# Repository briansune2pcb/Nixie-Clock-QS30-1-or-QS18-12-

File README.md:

# Nixie-Clock-QS30-1-or-QS18-12-

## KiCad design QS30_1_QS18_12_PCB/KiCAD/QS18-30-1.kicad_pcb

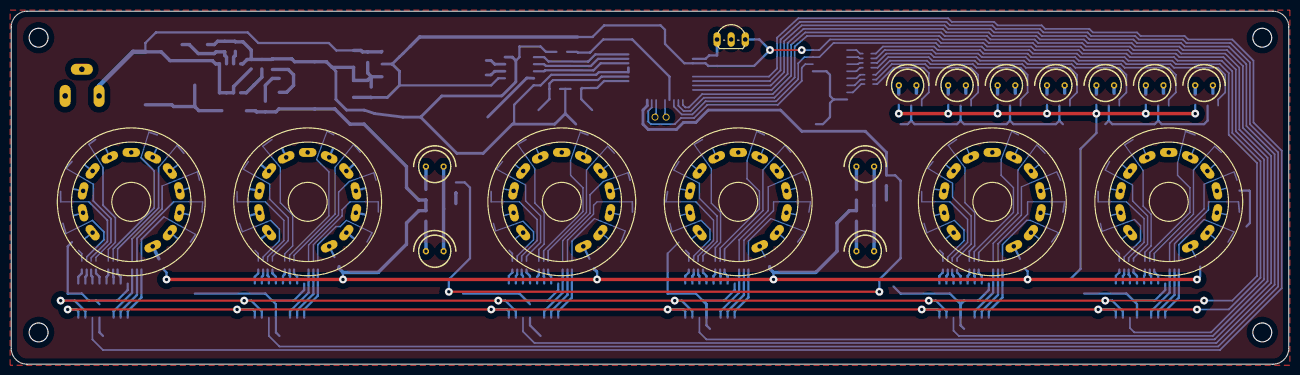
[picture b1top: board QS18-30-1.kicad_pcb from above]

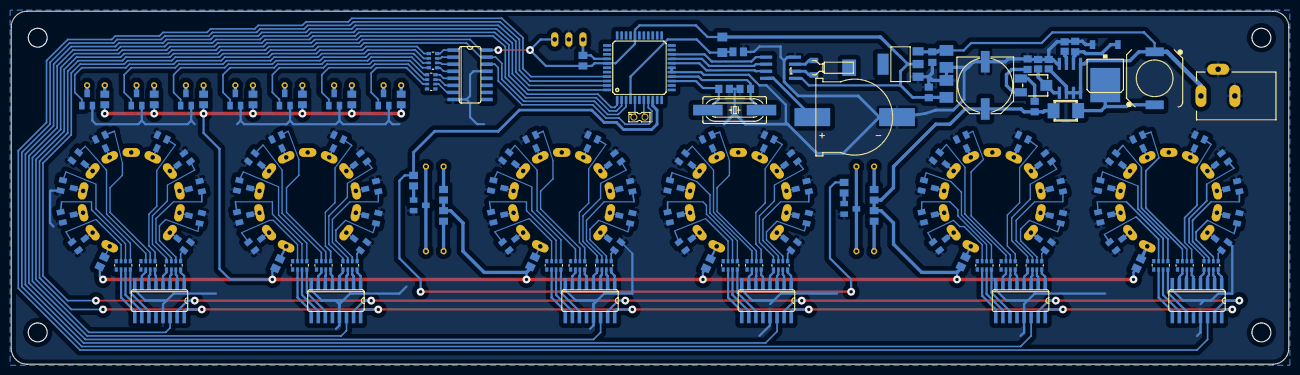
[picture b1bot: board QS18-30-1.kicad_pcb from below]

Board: 2 copper layers, 229.9 x 63.5 mm, 162 parts (144 on the bottom side), 253 nets.

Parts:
C1, C2, C3, C5, C6, C8, C10: C0805
C4: C1206
C7, C9: B_3528-21R
C11: PANASONIC_G
D1: SMB
IC1, IC2, IC3, IC4, IC5, IC6, IC9: 4017D; SO16
IC7: MC34063AD; SOIC8
J1: DCJ0303
L2: DR1033
MCU1: AT89S51-33P; TQFP44
N1, N2, N3, N4, N5, N6, N7, N8, N9, N10: IN-3
N11: Mon; IN-3
Q1: HC49UP
Q3: IRFR5305; D-PAK_TO252AA
R1, R2, R3, R4, R16, R17, R18, R19, R24, R25, R26, R27, R30, R31, R32, R33, R34, R35, R43, R44: EXB38V
R5, R6, R7, R8, R9, R10, R14, R15, R20, R21, R22, R28, R29, R36, R37, R38, R39, R40, R41, R42, R45: M0805
R11, R12, R13: R0805
R23: RTRIM3374
REG2: REG1117; SOT223
T1, T2, T3, T4, T5, T6, T7, T8, T9, T10, T11, T12, T13, T14, T15, T16, T17, T18, T19, T20, T21, T22, T23, T24, T25, T26, T27, T28, T29, T30, T31, T32, T33, T34, T35, T36, T37, T38, T39, T40, T41, T42, T43, T44, T45, T46, T47, T48, T49, T50, T51, T52, T53, T54, T55, T56, T57, T58, T59, T60, T61, T62, T63, T64, T65, T66, T67, T68, T69: SOT23-BEC
TUBE1, TUBE2, TUBE3, TUBE4, TUBE5, TUBE6: QS30-1R1; QS30-1_V3
U$1: DS1302SOP08; SOP08
U$2: 1220BATTERY_SF; 1220BATTERY
U$3: MS1V-T1K-6P; MS1V-T1K
U$4: HX1838; TO92-
X1: 332-02

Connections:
170V: C11.+, D1.1, R5.2, R6.2, R7.2, R8.2, R9.2, R10.2, R11.2, R14.2, R15.2, R28.2, R29.2, R36.2, R37.2, R38.2, R39.2, R40.2, R41.2, R42.2
+5V: C4.2, C9.+, C10.1, IC1.16, IC2.16, IC3.16, IC4.16, IC5.16, IC6.16, IC9.16, MCU1.29, MCU1.38, R45.2, REG2.2, U$1.1, U$4.1
+12V: C2.1, C7.+, C8.1, IC7.1, IC7.6, IC7.7, IC7.8, J1.1, L2.1, REG2.3
CLK_D0: IC9.14, MCU1.8
CLK_H0: IC1.14, MCU1.41
CLK_H1: IC2.14, MCU1.42
CLK_M0: IC3.14, MCU1.43
CLK_M1: IC4.14, MCU1.44
CLK_S0: IC5.14, MCU1.1
CLK_S1: IC6.14, MCU1.2
CS: MCU1.20, U$1.5
DAY0: R43.1, T63.B
DAY1: R43.2, T64.B
DAY2: R43.3, T65.B
DAY3: R43.4, T66.B
DAY4: R44.1, T67.B
DAY5: R44.2, T68.B
DAY6: R44.3, T69.B
DOT: MCU1.9, R20.2, R21.2
GND: C1.2, C2.2, C3.2, C5.2, C6.1, C7.-, C8.2, C9.-, C10.2, C11.-, IC1.8, IC1.13, IC2.8, IC2.13, IC3.8, IC3.13, IC4.8, IC4.13, IC5.8, IC5.13, IC6.8, IC6.13, IC7.4, IC9.8, IC9.13, J1.2, J1.3, MCU1.16, MCU1.17, Q3.3, R12.1, R13.1, R22.1, REG2.1, T1.E, T2.E, T3.E, T4.E, T5.E, T6.E, T7.E, T8.E, T9.E, T10.E, T11.E, T12.E, T13.E, T14.E, T15.E, T16.E, T17.E, T18.E, T19.E, T20.E, T21.E, T22.E, T23.E, T24.E, T25.E, T26.E, T27.E, T28.E, T29.E, T30.E, T31.E, T32.E, T33.E, T34.E, T35.E, T36.E, T37.E, T38.E, T39.E, T40.E, T41.E, T42.E, T43.E, T44.E, T45.E, T46.E, T47.E, T48.E, T49.E, T50.E, T51.E, T52.E, T53.E, T54.E, T55.E, T56.E, T57.E, T58.E, T59.E, T60.E, T61.E, T62.E, T63.E, T64.E, T65.E, T66.E, T67.E, T68.E, T69.E, U$1.4, U$2.-, U$4.2
unnamed: C5.1, MCU1.14, Q1.1
unnamed: C6.2, MCU1.15, Q1.2
unnamed: R1.1, T2.B
unnamed: R1.2, T3.B
unnamed: R1.3, T4.B
unnamed: R4.1, T12.B
unnamed: R1.4, T5.B
unnamed: R2.1, T6.B
unnamed: R2.2, T7.B
unnamed: R2.3, T8.B
unnamed: R3.1, T9.B
unnamed: R3.2, T10.B
unnamed: R3.3, T1.B
unnamed: R4.2, T13.B
unnamed: R4.3, T14.B
unnamed: R4.4, T15.B
unnamed: R16.1, T16.B
unnamed: R16.2, T17.B
unnamed: R16.3, T18.B
unnamed: R17.1, T19.B
unnamed: R17.2, T20.B
unnamed: R17.3, T11.B
unnamed: R14.1, TUBE3.A
unnamed: R15.1, TUBE4.A
unnamed: R5.1, TUBE1.A
unnamed: R18.1, T22.B
unnamed: R6.1, TUBE2.A
unnamed: R18.2, T23.B
unnamed: R18.3, T24.B
unnamed: R18.4, T25.B
unnamed: R19.1, T26.B
unnamed: R19.2, T27.B
unnamed: R19.3, T28.B
unnamed: R24.1, T29.B
unnamed: R24.2, T30.B
unnamed: R24.3, T21.B
unnamed: R25.1, T32.B
unnamed: R25.2, T33.B
unnamed: R25.3, T34.B
unnamed: R25.4, T35.B
unnamed: R26.1, T36.B
unnamed: R26.2, T37.B
unnamed: R26.3, T38.B
unnamed: R27.1, T39.B
unnamed: R27.2, T40.B
unnamed: R27.3, T31.B
unnamed: IC3.1, R18.8
unnamed: IC3.2, R18.7
unnamed: N3.A, R7.1
unnamed: N1.A, R8.1
unnamed: N2.A, R9.1
unnamed: N4.A, R10.1
unnamed: IC7.2, Q3.1, R13.2
unnamed: MCU1.5, X1.1
unnamed: C1.1, IC7.3
unnamed: C3.1, IC7.5, R23.2
unnamed: D1.2, L2.2, Q3.4
unnamed: IC3.3, R18.6
unnamed: IC3.4, R18.5
unnamed: IC3.5, R19.8
unnamed: MCU1.7, X1.2
unnamed: IC3.6, R19.7
unnamed: IC3.7, R19.6
unnamed: IC3.9, R24.6
unnamed: IC3.11, R24.8
unnamed: IC3.10, R24.7
unnamed: IC4.3, R25.6
unnamed: IC4.1, R25.8
unnamed: IC4.2, R25.7
unnamed: IC4.11, R27.8
unnamed: IC4.9, R27.6
unnamed: IC4.10, R27.7
unnamed: IC4.4, R25.5
unnamed: IC4.5, R26.8
unnamed: IC4.6, R26.7
unnamed: IC4.7, R26.6
unnamed: IC1.1, R1.8
unnamed: IC1.2, R1.7
unnamed: IC1.3, R1.6
unnamed: IC1.4, R1.5
unnamed: IC1.5, R2.8
unnamed: IC1.6, R2.7
unnamed: IC1.7, R2.6
unnamed: IC1.11, R3.8
unnamed: IC1.10, R3.7
unnamed: R28.1, TUBE5.A
unnamed: IC1.9, R3.6
unnamed: R29.1, TUBE6.A
unnamed: N2.K, N4.K, T61.C
unnamed: R20.1, T61.B
unnamed: N1.K, N3.K, T62.C
unnamed: R21.1, T62.B
unnamed: IC2.1, R4.8
unnamed: IC2.2, R4.7
unnamed: IC2.3, R4.6
unnamed: IC2.4, R4.5
unnamed: IC2.5, R16.8
unnamed: U$1.8, U$2.+
unnamed: IC2.6, R16.7
unnamed: IC2.7, R16.6
unnamed: IC2.11, R17.8
unnamed: IC2.10, R17.7
unnamed: U$1.2, U$3.P$1
unnamed: C4.1, MCU1.4, R22.2
unnamed: U$1.3, U$3.P$2
unnamed: IC2.9, R17.6
unnamed: R30.1, T42.B
unnamed: R30.2, T43.B
unnamed: R30.3, T44.B
unnamed: R30.4, T45.B
unnamed: R31.1, T46.B
unnamed: R31.2, T47.B
unnamed: R31.3, T48.B
unnamed: R32.1, T49.B
unnamed: R32.2, T50.B
unnamed: R32.3, T41.B
unnamed: R33.1, T52.B
unnamed: R33.2, T53.B
unnamed: R33.3, T54.B
unnamed: R33.4, T55.B
unnamed: R34.1, T56.B
unnamed: R34.2, T57.B
unnamed: R34.3, T58.B
unnamed: R35.1, T59.B
unnamed: R35.2, T60.B
unnamed: R35.3, T51.B
unnamed: IC5.1, R30.8
unnamed: IC5.2, R30.7
unnamed: IC5.3, R30.6
unnamed: IC5.4, R30.5
unnamed: IC5.5, R31.8
unnamed: IC5.6, R31.7
unnamed: IC5.7, R31.6
unnamed: IC5.9, R32.6
unnamed: IC5.11, R32.8
unnamed: IC5.10, R32.7
unnamed: IC6.3, R33.6
unnamed: IC6.1, R33.8
unnamed: IC6.2, R33.7
unnamed: IC6.11, R35.8
unnamed: IC6.9, R35.6
unnamed: IC6.10, R35.7
unnamed: IC6.4, R33.5
unnamed: IC6.5, R34.8
unnamed: IC6.6, R34.7
unnamed: IC6.7, R34.6
unnamed: N5.K, T63.C
unnamed: N6.K, T64.C
unnamed: N7.K, T65.C
unnamed: N8.K, T66.C
unnamed: N9.K, T67.C
unnamed: N10.K, T68.C
unnamed: N11.K, T69.C
unnamed: N5.A, R36.1
unnamed: N6.A, R37.1
unnamed: N8.A, R39.1
unnamed: N11.A, R42.1
unnamed: N10.A, R41.1
unnamed: N9.A, R40.1
unnamed: N7.A, R38.1
unnamed: R11.1, R23.1
unnamed: R12.2, R23.3
unnamed: IC9.1, R43.8
unnamed: IC9.2, R43.7
unnamed: IC9.3, R43.6
unnamed: IC9.4, R43.5
unnamed: IC9.7, R44.6
unnamed: IC9.5, R44.8
unnamed: IC9.6, R44.7
QS18_1_0: T1.C, TUBE1.0
QS18_1_1: T2.C, TUBE1.1
QS18_1_2: T3.C, TUBE1.2
QS18_1_3: T4.C, TUBE1.3
QS18_1_4: T5.C, TUBE1.4
QS18_1_5: T6.C, TUBE1.5
QS18_1_6: T7.C, TUBE1.6
QS18_1_7: T8.C, TUBE1.7
QS18_1_8: T9.C, TUBE1.8
QS18_1_9: T10.C, TUBE1.9
QS18_2_0: T11.C, TUBE2.0
QS18_2_1: T12.C, TUBE2.1
QS18_2_2: T13.C, TUBE2.2
QS18_2_3: T14.C, TUBE2.3
QS18_2_4: T15.C, TUBE2.4
QS18_2_5: T16.C, TUBE2.5
QS18_2_6: T17.C, TUBE2.6
QS18_2_7: T18.C, TUBE2.7
QS18_2_8: T19.C, TUBE2.8
QS18_2_9: T20.C, TUBE2.9
QS18_3_0: T21.C, TUBE3.0
QS18_3_1: T22.C, TUBE3.1
QS18_3_2: T23.C, TUBE3.2
QS18_3_3: T24.C, TUBE3.3
QS18_3_4: T25.C, TUBE3.4
QS18_3_5: T26.C, TUBE3.5
QS18_3_6: T27.C, TUBE3.6
QS18_3_7: T28.C, TUBE3.7
QS18_3_8: T29.C, TUBE3.8
QS18_3_9: T30.C, TUBE3.9
QS18_4_0: T31.C, TUBE4.0
QS18_4_1: T32.C, TUBE4.1
QS18_4_2: T33.C, TUBE4.2
QS18_4_3: T34.C, TUBE4.3
QS18_4_4: T35.C, TUBE4.4
QS18_4_5: T36.C, TUBE4.5
QS18_4_6: T37.C, TUBE4.6
QS18_4_7: T38.C, TUBE4.7
QS18_4_8: T39.C, TUBE4.8
QS18_4_9: T40.C, TUBE4.9
QS18_5_0: T41.C, TUBE5.0
QS18_5_1: T42.C, TUBE5.1
QS18_5_2: T43.C, TUBE5.2
QS18_5_3: T44.C, TUBE5.3
QS18_5_4: T45.C, TUBE5.4
QS18_5_5: T46.C, TUBE5.5
QS18_5_6: T47.C, TUBE5.6
QS18_5_7: T48.C, TUBE5.7
QS18_5_8: T49.C, TUBE5.8
QS18_5_9: T50.C, TUBE5.9
QS18_6_0: T51.C, TUBE6.0
QS18_6_1: T52.C, TUBE6.1
QS18_6_2: T53.C, TUBE6.2
QS18_6_3: T54.C, TUBE6.3
QS18_6_4: T55.C, TUBE6.4
QS18_6_5: T56.C, TUBE6.5
QS18_6_6: T57.C, TUBE6.6
QS18_6_7: T58.C, TUBE6.7
QS18_6_8: T59.C, TUBE6.8
QS18_6_9: T60.C, TUBE6.9
RST4017: IC1.15, IC2.15, IC3.15, IC4.15, IC5.15, IC6.15, IC9.15, MCU1.3
SCK: MCU1.18, U$1.7
SD: MCU1.37, R45.1, U$4.3
SDIN: MCU1.19, U$1.6
